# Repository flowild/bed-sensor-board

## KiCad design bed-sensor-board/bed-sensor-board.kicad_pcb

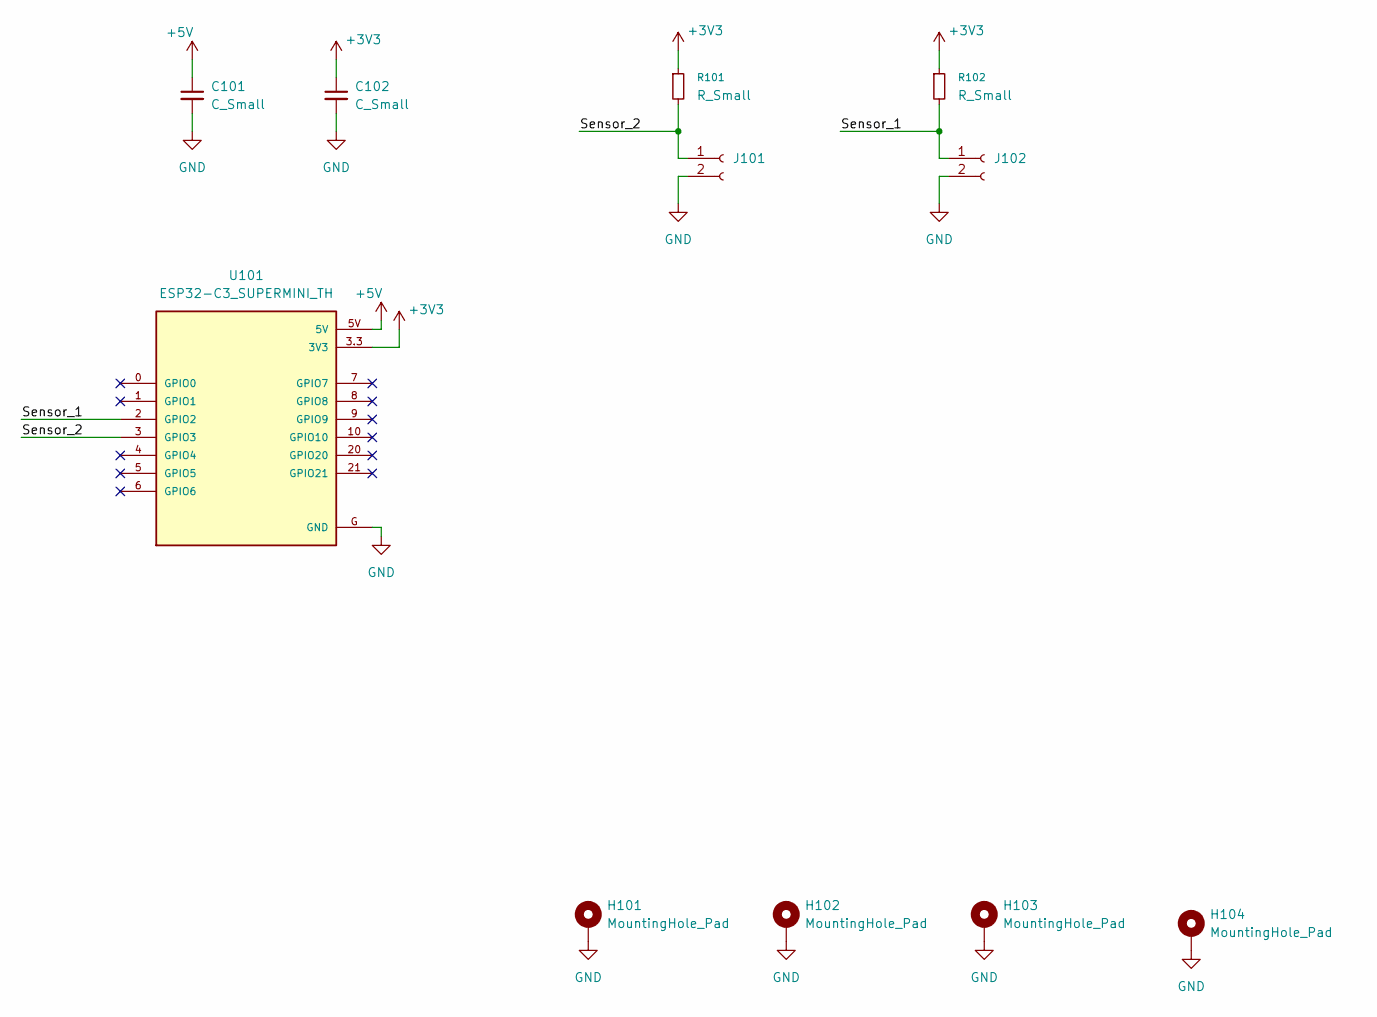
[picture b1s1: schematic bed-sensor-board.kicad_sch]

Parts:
C101, C102: C_Small; C_0805_2012Metric_Pad1.18x1.45mm_HandSolder
H101, H102, H103, H104: MountingHole_Pad; MountingHole_3.2mm_M3_DIN965_Pad
J101, J102: Conn_01x02_Socket; SolderWire-1.5sqmm_1x02_P6mm_D1.7mm_OD3mm
R101, R102: R_Small; R_0805_2012Metric_Pad1.20x1.40mm_HandSolder
U101: ESP32-C3_SUPERMINI_TH; MODULE_ESP32-C3_SUPERMINI_TH

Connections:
+3V3: C102.1, R101.1, R102.1, U101.3.3 (3V3)
+5V: C101.1, U101.5V
/Sensor_1: J102.1, R102.2, U101.2 (GPIO2)
/Sensor_2: J101.1, R101.2, U101.3 (GPIO3)
GND: C101.2, C102.2, H101.1, H102.1, H103.1, H104.1, J101.2, J102.2, U101.G (GND)

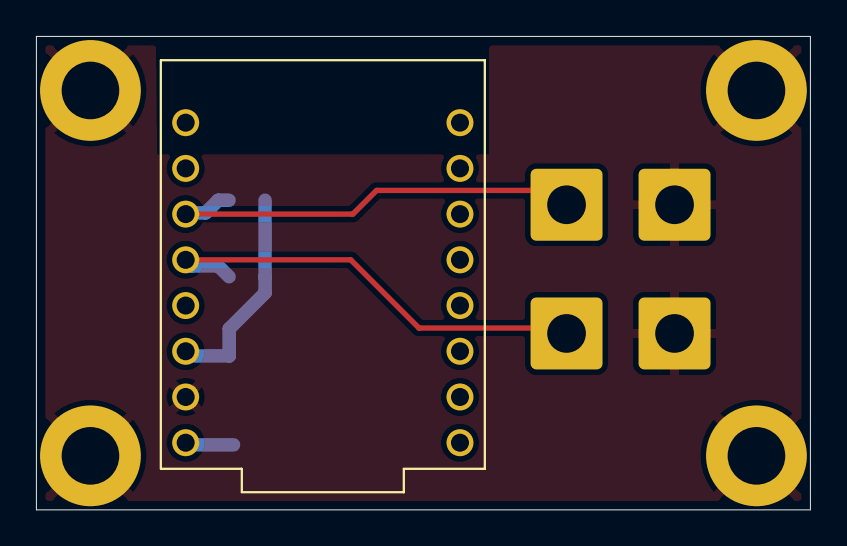
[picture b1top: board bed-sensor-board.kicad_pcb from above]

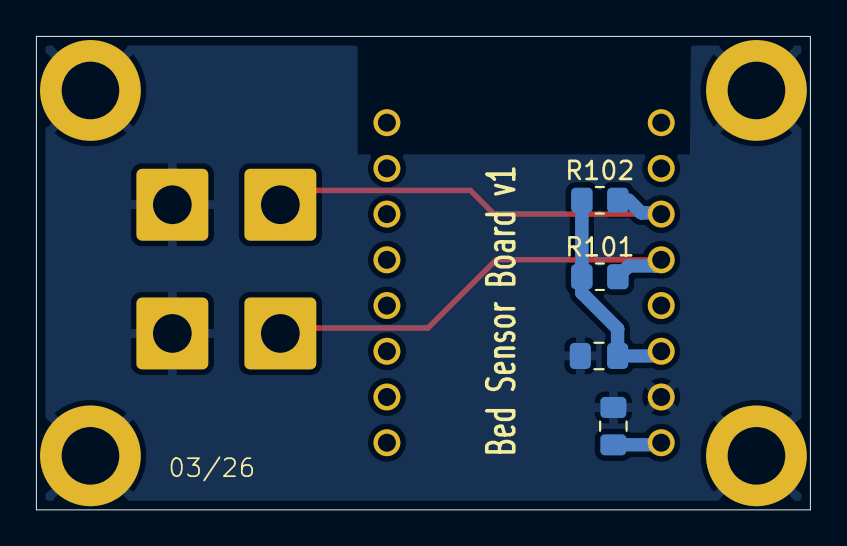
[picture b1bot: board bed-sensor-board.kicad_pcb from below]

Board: 2 copper layers, 43.0 x 26.3 mm, 11 parts (4 on the bottom side), 5 nets.

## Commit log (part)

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2026-03-28 project initial
2026-03-28 fab files v1
